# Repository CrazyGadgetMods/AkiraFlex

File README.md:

# AkiraFlex
AkiraFlex is an N64 RDRAM termination flex PCB, designed to be a low-profile replacement for the stock expansion port + trimmed jumper pak combo commonly used in existing N64 portables. It was inspired by the ["Akira Method"](https://bitbuilt.net/forums/index.php?threads/lockdown-64.4175/post-46301) of digging up the expansion port pads and deadbugging the RDRAM termination circuit.

\

## Installation
Components for the flex can either be pulled from an original N64 jumper / expansion pak, or can be bought brand new. All RAs are 1206-sized 51 Ohm, all caps are 0603-sized 1uF.

This flex was originally designed around a NUS-CPU-03 board, which has test points on the RDRAM traces between the RAM and the expansion port. If you are using this on a non-Rev 3 board (such as the Rev 4 board I installed in on here), you will need to scratch the traces as shown. Additionally, the VREF and VTERM vias must be scratched / tinned. Though apparently not necessary according to some testing Cy (of the BitBuilt Forums) has done, it is best practice to dig up the existing expansion port pads, as they will act as stubs for the RDRAM; not digging them up may lead to the board not booting / possible instabilities in-game. Once all the necessary vias / traces have been scratched / tinned / dug up, the flex can be installed on the board. Once installed, run a magnet wire from the pad shown below and the bottom of R33 on the N64 (rambus clock output from the mx8330).

## Testing

## Purchasing
If interested in purchasing an AkiraFlex kit (blank flex + RAs and capacitors), [I am selling them on my Etsy store!](https://www.etsy.com/listing/1780345019)

## Credits
- [Akira](https://bitbuilt.net/forums/index.php?members/akira.1105/): [creating the original method for deadbugging the RDRAM termination circuit](https://bitbuilt.net/forums/index.php?threads/lockdown-64.4175/post-46301)
- [Noah](https://bitbuilt.net/forums/index.php?members/noah.1/): [inspiration from his unfinished Terminator 64 flex](https://bitbuilt.net/forums/index.php?threads/fusion64.3139/post-37558)
- [Cy](https://bitbuilt.net/forums/index.php?members/cy.7203/): [inspiration from his Terminator 64 flex](https://bitbuilt.net/forums/index.php?threads/ashida-64-working-title-n64-portable.5529/post-64147)
- [YveltalGriffin](https://github.com/mackieks): answering my many, many, *many* questions during my N64 anatomy deep-dive and helping me understand RDRAM / the Akira Method
- [BitBuilt](https://bitbuilt.net/): Being the best modding community out there!

## License
Solderpad Hardware License v2.1

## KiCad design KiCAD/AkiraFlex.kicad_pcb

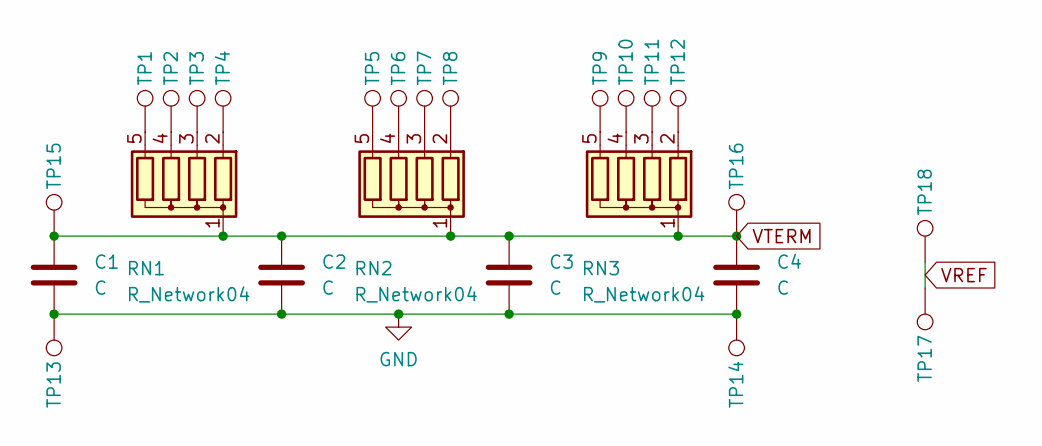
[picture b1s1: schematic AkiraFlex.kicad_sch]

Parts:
C1, C2, C3, C4: C; C_0603_1608Metric
RN1, RN2, RN3: R_Network04; R_Array_Concave_4x0603
TP1, TP2, TP3, TP4, TP5, TP6, TP7, TP8, TP9, TP10, TP11, TP12, TP18: TestPoint; RAM Via
TP13, TP14: TestPoint; RAM GND
TP15, TP16, TP17: TestPoint; RAM Via 2

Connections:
GND: C1.2, C2.2, C3.2, C4.2, TP13.1, TP14.1
unnamed: RN1.2 (R1), TP4.1
unnamed: RN1.3 (R2), TP3.1
unnamed: RN1.4 (R3), TP2.1
unnamed: RN1.5 (R4), TP1.1
unnamed: RN2.2 (R1), TP8.1
unnamed: RN2.3 (R2), TP7.1
unnamed: RN2.4 (R3), TP6.1
unnamed: RN2.5 (R4), TP5.1
unnamed: RN3.2 (R1), TP12.1
unnamed: RN3.3 (R2), TP11.1
unnamed: RN3.4 (R3), TP10.1
unnamed: RN3.5 (R4), TP9.1
VREF: TP17.1, TP18.1
VTERM: C1.1, C2.1, C3.1, C4.1, RN1.1 (common), RN2.1 (common), RN3.1 (common), TP15.1, TP16.1

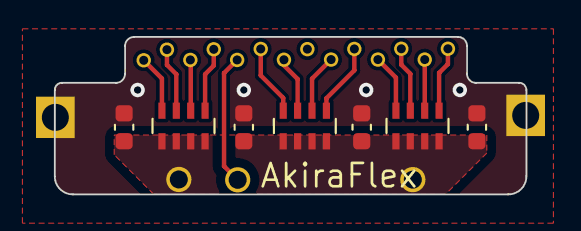
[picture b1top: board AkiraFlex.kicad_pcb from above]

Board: 2 copper layers, 26.2 x 8.8 mm, 25 parts (0 on the bottom side), 15 nets.

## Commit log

2024-05-08 init
